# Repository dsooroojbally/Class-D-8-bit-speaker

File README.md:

First personal project, implementing a ESP-32 for a simple speaker system in KiCAD.

Main components: ESP-32, Gate-Driver IC, 40 W speaker, Voltage Regulator.

Due to corrupted files, wiring of board is partially incomplete also some component models may not appear.

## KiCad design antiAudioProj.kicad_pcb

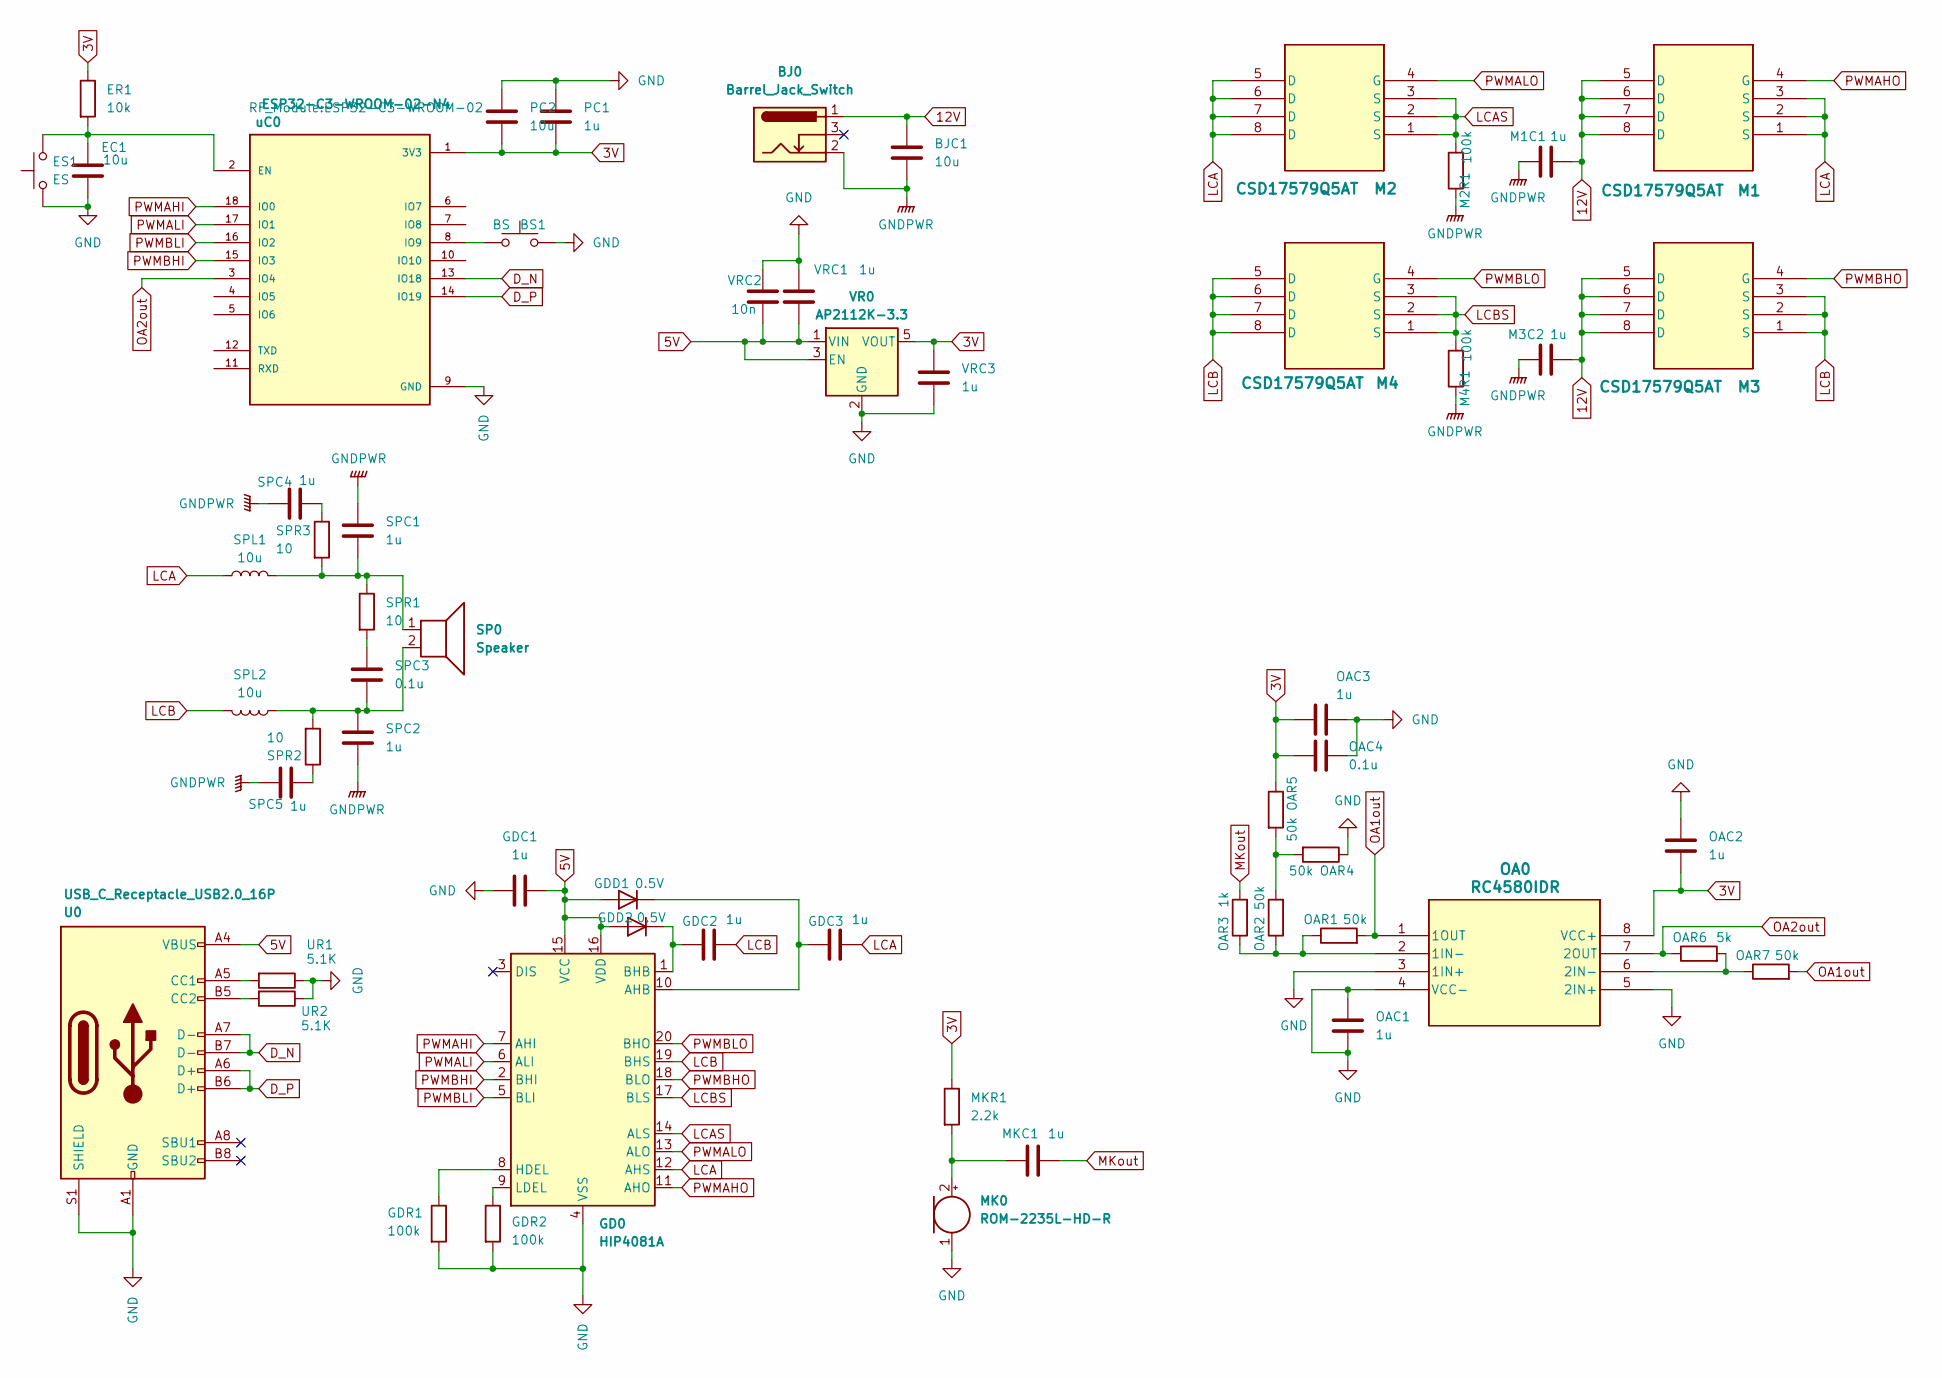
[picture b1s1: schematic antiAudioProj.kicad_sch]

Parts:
BJ0: Barrel_Jack_Switch; BarrelJack_CUI_PJ-102AH_Horizontal
BJC1: 10u; C_0805_2012Metric
BS1: BS; SW_SPST_PTS810
EC1: 10u; C_0805_2012Metric_Pad1.18x1.45mm_HandSolder
ER1: 10k; R_0805_2012Metric_Pad1.20x1.40mm_HandSolder
ES1: ES; SW_SPST_PTS810
GD0: HIP4081A; SOIC-20W_7.5x12.8mm_P1.27mm
GDC1, GDC2, GDC3: 1u; C_0805_2012Metric
GDD1, GDD2: 0.5V; D_0805_2012Metric
GDR1, GDR2: 100k; R_0805_2012Metric
M1, M2, M3, M4: CSD17579Q5AT; DQJ8_TEX
M1C1, M3C2: 1u; C_0805_2012Metric
M2R1, M4R1: 100k; R_0805_2012Metric
MK0: ROM-2235L-HD-R; POM-2244P-C3310-2-R
MKC1: 1u; C_0805_2012Metric_Pad1.18x1.45mm_HandSolder
MKR1: 2.2k; R_0805_2012Metric_Pad1.20x1.40mm_HandSolder
OA0: RC4580IDR; D8
OAC1, OAC2, OAC3: 1u; C_0805_2012Metric_Pad1.18x1.45mm_HandSolder
OAC4: 0.1u; C_0805_2012Metric_Pad1.18x1.45mm_HandSolder
OAR1, OAR2, OAR4, OAR5, OAR7: 50k; R_0805_2012Metric
OAR3: 1k; R_0805_2012Metric
OAR6: 5k; R_0805_2012Metric
PC1: 1u; C_0805_2012Metric_Pad1.18x1.45mm_HandSolder
PC2: 10u; C_0805_2012Metric_Pad1.18x1.45mm_HandSolder
SP0: Speaker; R_4020_10251Metric_Pad1.65x5.30mm_HandSolder
SPC1, SPC2, SPC4, SPC5: 1u; C_0805_2012Metric_Pad1.18x1.45mm_HandSolder
SPC3: 0.1u; C_0805_2012Metric
SPL1, SPL2: 10u; L_Bourns_SRR1208_12.7x12.7mm
SPR1: 10; R_0805_2012Metric_Pad1.20x1.40mm_HandSolder
SPR2, SPR3: 10; R_0805_2012Metric
U0: USB_C_Receptacle_USB2.0_16P; USB_C_Receptacle_GCT_USB4105-xx-A_16P_TopMnt_Horizontal
UR1, UR2: 5.1K; R_0805_2012Metric
VR0: AP2112K-3.3; SOT-23-5
VRC1, VRC3: 1u; C_0805_2012Metric
VRC2: 10n; C_0805_2012Metric
uC0: ESP32-C3-WROOM-02-N4; ESP32-C3-WROOM-02

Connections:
3V: ER1.1, MKR1.1, OA0.8 (VCC+), OAC2.2, OAC3.1, OAC4.1, OAR5.1, PC1.2, PC2.2, VR0.5 (VOUT), VRC3.1, uC0.1 (3V3)
5V: GD0.15 (VCC), GD0.16 (VDD), GDC1.2, GDD1.2 (A), GDD2.2 (A), U0.A4 (VBUS), U0.A9 (VBUS), U0.B4 (VBUS), U0.B9 (VBUS), VR0.1 (VIN), VR0.3 (EN), VRC1.2, VRC2.2
12V: BJ0.1, BJC1.1, M1.5 (D), M1.6 (D), M1.7 (D), M1.8 (D), M1C1.2, M3.5 (D), M3.6 (D), M3.7 (D), M3.8 (D), M3C2.2
D_N: U0.A7 (D-), U0.B7 (D-), uC0.13 (IO18)
D_P: U0.A6 (D+), U0.B6 (D+), uC0.14 (IO19)
GND: BS1.2, EC1.2, ES1.1, GD0.4 (VSS), GDC1.1, GDR1.2, GDR2.2, MK0.1 (-), OA0.3 (1IN+), OA0.4 (VCC-), OA0.5 (2IN+), OAC1.1, OAC1.2, OAC2.1, OAC3.2, OAC4.2, OAR4.1, PC1.1, PC2.1, U0.A1 (GND), U0.A12 (GND), U0.B1 (GND), U0.B12 (GND), U0.S1 (SHIELD), UR1.1, UR2.1, VR0.2 (GND), VRC1.1, VRC2.1, VRC3.2, uC0.9 (GND)
GNDPWR: BJ0.2, BJC1.2, M1C1.1, M2R1.1, M3C2.1, M4R1.1, SPC1.1, SPC2.2, SPC4.1, SPC5.1
LCA: GD0.12 (AHS), GDC3.2, M1.1 (S), M1.2 (S), M1.3 (S), M2.5 (D), M2.6 (D), M2.7 (D), M2.8 (D), SPL1.1
LCAS: GD0.14 (ALS), M2.1 (S), M2.2 (S), M2.3 (S), M2R1.2
LCB: GD0.19 (BHS), GDC2.2, M3.1 (S), M3.2 (S), M3.3 (S), M4.5 (D), M4.6 (D), M4.7 (D), M4.8 (D), SPL2.2
LCBS: GD0.17 (BLS), M4.1 (S), M4.2 (S), M4.3 (S), M4R1.2
MKout: MKC1.2, OAR3.2
unnamed: GD0.10 (AHB), GDC3.1, GDD1.1 (K)
unnamed: GD0.1 (BHB), GDC2.1, GDD2.1 (K)
unnamed: GD0.8 (HDEL), GDR1.1
unnamed: GD0.9 (LDEL), GDR2.1
unnamed: MK0.2 (+), MKC1.1, MKR1.2
unnamed: OA0.2 (1IN-), OAR1.1, OAR2.1, OAR3.1
unnamed: OA0.6 (2IN-), OAR6.2, OAR7.1
unnamed: OAR2.2, OAR4.2, OAR5.2
unnamed: SP0.1, SPC1.2, SPL1.2, SPR1.1, SPR3.2
unnamed: SP0.2, SPC2.1, SPC3.2, SPL2.1, SPR2.2
unnamed: SPC3.1, SPR1.2
unnamed: SPC4.2, SPR3.1
unnamed: SPC5.2, SPR2.1
unnamed: U0.A5 (CC1), UR1.2
unnamed: U0.B5 (CC2), UR2.2
unnamed: EC1.1, ER1.2, ES1.2, uC0.2 (EN)
unnamed: BS1.1, uC0.8 (IO9)
OA1out: OA0.1 (1OUT), OAR1.2, OAR7.2
OA2out: OA0.7 (2OUT), OAR6.1, uC0.3 (IO4)
PWMAHI: GD0.7 (AHI), uC0.18 (IO0)
PWMAHO: GD0.11 (AHO), M1.4 (G)
PWMALI: GD0.6 (ALI), uC0.17 (IO1)
PWMALO: GD0.13 (ALO), M2.4 (G)
PWMBHI: GD0.2 (BHI), uC0.15 (IO3)
PWMBHO: GD0.18 (BLO), M3.4 (G)
PWMBLI: GD0.5 (BLI), uC0.16 (IO2)
PWMBLO: GD0.20 (BHO), M4.4 (G)

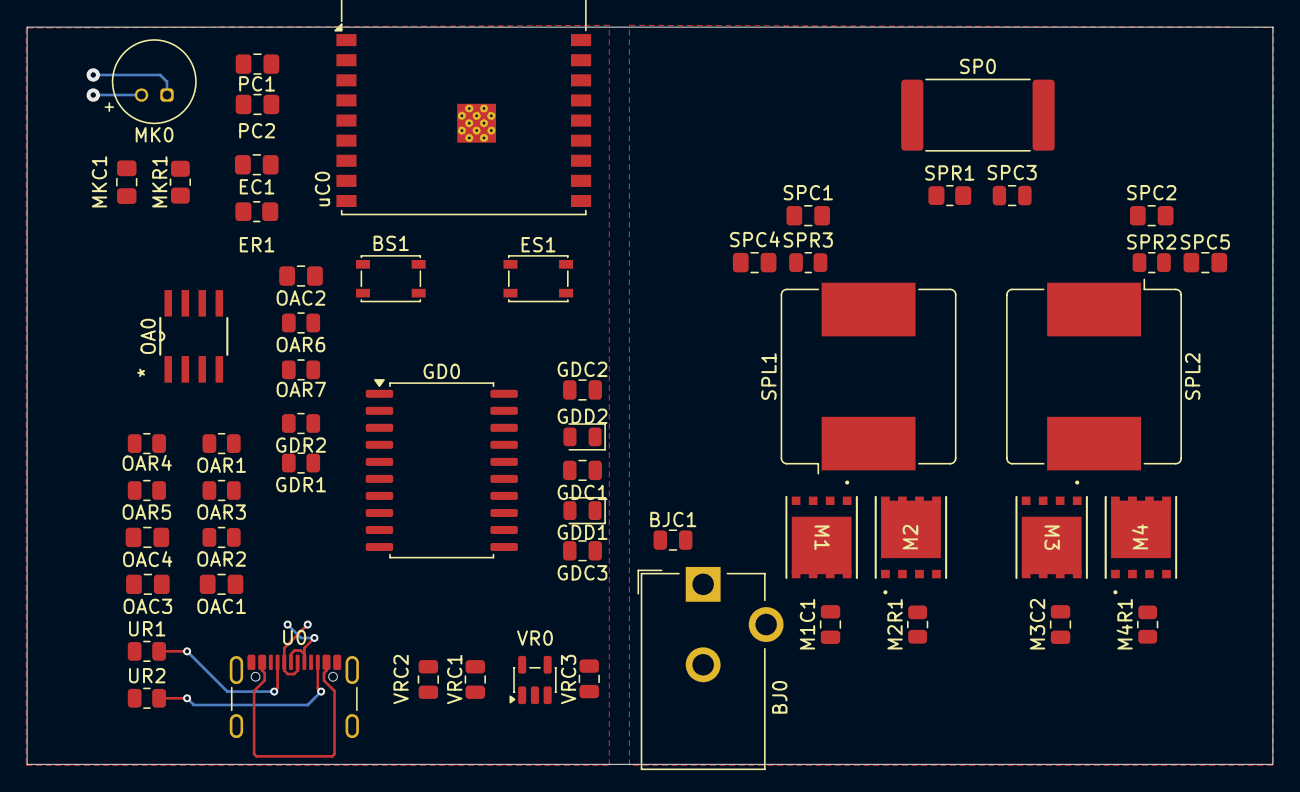
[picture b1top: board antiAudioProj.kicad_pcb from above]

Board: 2 copper layers, 92.9 x 55.0 mm, 58 parts (0 on the bottom side), 39 nets.
